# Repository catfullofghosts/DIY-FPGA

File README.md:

# diy_fpga
A discrete component FPGA designed from scratch

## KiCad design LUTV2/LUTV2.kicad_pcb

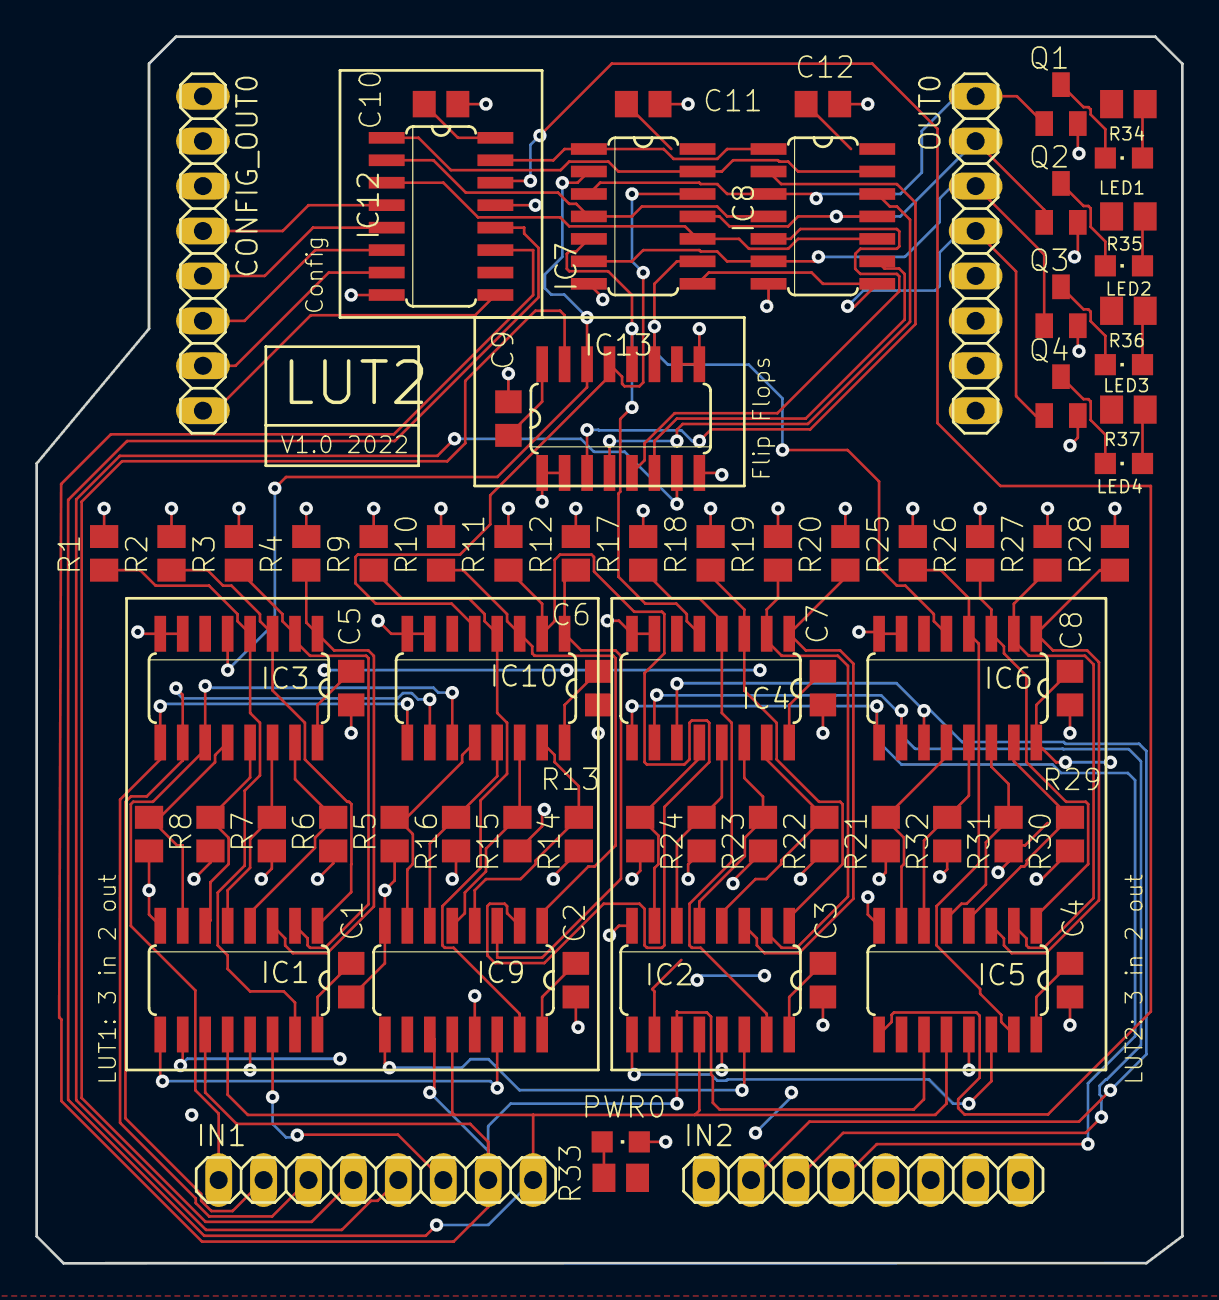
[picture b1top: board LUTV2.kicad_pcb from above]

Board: 2 copper layers, 64.8 x 69.3 mm, 74 parts (0 on the bottom side), 79 nets.

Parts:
C1, C2, C3, C4, C5, C6, C7, C8, C9, C10, C11, C12: C0805_348
CONFIG_OUT0: 1X08_325
IC1, IC2, IC5, IC9, IC12: 74HC595D; SO16
IC3, IC4, IC6, IC10: 74HC251D; SO16
IC7: 74HC126D; SO14
IC8: 74HC125D; SO14
IC13: 74HC173D; SO16
IN1, IN2: 1X08_325
LED1, LED2, LED3, LED4: CHIPLED_0805_420
OUT0: 1X08_325
PWR0: CHIPLED_0805_420
Q1, Q2, Q3, Q4: SOT23_420
R1, R2, R3, R4, R5, R6, R7, R8, R9, R10, R11, R12, R13, R14, R15, R16, R17, R18, R19, R20, R21, R22, R23, R24, R25, R26, R27, R28, R29, R30, R31, R32: M0805_348
R33, R34, R35, R36, R37: 220; M0805_348

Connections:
A: IC3.11, IC10.11, IN1.1
A2: IC4.11, IC6.11, IN2.2
ASYNC_0: IC7.1, IC8.1, IC12.15
ASYNC_1: IC7.13, IC8.13, IC12.1
ASYNC_2: IC7.4, IC8.4, IC12.2
ASYNC_3: IC7.10, IC8.10, IC12.3
B: IC3.10, IC10.10, IN1.2
B2: IC4.10, IC6.10, IN2.3
C: IC3.9, IC10.9, IN1.3
C2: IC4.9, IC6.9, IN2.4
DCLK: IC13.7, IN1.5
GND: C1.2, C2.2, C3.2, C4.2, C5.2, C6.2, C7.2, C8.2, C9.2, C10.2, C11.2, C12.2, CONFIG_OUT0.2, IC1.8, IC1.13, IC2.8, IC2.13, IC3.7, IC3.8, IC4.7, IC4.8, IC5.8, IC5.13, IC6.7, IC6.8, IC7.7, IC8.7, IC9.8, IC9.13, IC10.7, IC10.8, IC12.8, IC12.13, IC13.1, IC13.2, IC13.8, IC13.9, IC13.10, IN2.8, PWR0.C, Q1.2, Q2.2, Q3.2, Q4.2, R1.2, R2.2, R3.2, R4.2, R5.2, R6.2, R7.2, R8.2, R9.2, R10.2, R11.2, R12.2, R13.2, R14.2, R15.2, R16.2, R17.2, R18.2, R19.2, R20.2, R21.2, R22.2, R23.2, R24.2, R25.2, R26.2, R27.2, R28.2, R29.2, R30.2, R31.2, R32.2
LOAD: IC1.12, IC2.12, IC5.12, IC9.12, IC12.12, IN1.8
MISO: CONFIG_OUT0.8, IC12.9
MOSI: IC1.14, IN1.6
unnamed: IC1.15, IC3.4, R1.1
unnamed: IC1.1, IC3.3, R2.1
unnamed: IC1.2, IC3.2, R3.1
unnamed: IC1.4, IC3.15, R5.1
unnamed: IC1.5, IC3.14, R6.1
unnamed: IC1.6, IC3.13, R7.1
unnamed: IC1.7, IC3.12, R8.1
unnamed: IC3.5, IC7.2, IC13.14
unnamed: IC9.15, IC10.4, R9.1
unnamed: IC2.15, IC4.4, R17.1
unnamed: IC9.1, IC10.3, R10.1
unnamed: IC9.2, IC10.2, R11.1
unnamed: IC9.4, IC10.15, R13.1
unnamed: IC9.5, IC10.14, R14.1
unnamed: IC9.6, IC10.13, R15.1
unnamed: IC9.7, IC10.12, R16.1
unnamed: IC7.12, IC10.5, IC13.13
unnamed: IC1.9, IC9.14
unnamed: IC8.2, IC13.3
unnamed: IC2.14, IC9.9
unnamed: IC2.1, IC4.3, R18.1
unnamed: IC2.4, IC4.15, R21.1
unnamed: IC2.5, IC4.14, R22.1
unnamed: IC2.6, IC4.13, R23.1
unnamed: IC2.7, IC4.12, R24.1
unnamed: IC5.15, IC6.4, R25.1
unnamed: IC5.1, IC6.3, R26.1
unnamed: IC8.12, IC13.4
unnamed: IC9.3, IC10.1, R12.1
unnamed: IC1.3, IC3.1, R4.1
unnamed: IC5.4, IC6.15, R29.1
unnamed: IC5.5, IC6.14, R30.1
unnamed: IC5.6, IC6.13, R31.1
unnamed: IC5.7, IC6.12, R32.1
unnamed: IC2.9, IC5.14
unnamed: IC5.9, IC12.14
unnamed: IC6.5, IC7.9, IC13.11
unnamed: IC4.5, IC7.5, IC13.12
unnamed: IC5.2, IC6.2, R27.1
unnamed: IC5.3, IC6.1, R28.1
unnamed: IC2.2, IC4.2, R19.1
unnamed: IC2.3, IC4.1, R20.1
unnamed: CONFIG_OUT0.7, IC12.7
unnamed: CONFIG_OUT0.6, IC12.6
unnamed: CONFIG_OUT0.5, IC12.5
unnamed: CONFIG_OUT0.4, IC12.4
unnamed: IC8.5, IC13.5
unnamed: IC8.9, IC13.6
unnamed: PWR0.A, R33.1
unnamed: LED1.A, R34.1
unnamed: LED2.A, R35.1
unnamed: LED3.A, R36.1
unnamed: LED4.A, R37.1
unnamed: LED1.C, Q1.3
unnamed: LED2.C, Q2.3
unnamed: LED3.C, Q3.3
unnamed: LED4.C, Q4.3
O0: IC7.3, IC8.3, OUT0.1, Q1.1
O1: IC7.11, IC8.11, OUT0.2, Q2.1
O2: IC7.6, IC8.6, OUT0.3, Q3.1
O3: IC7.8, IC8.8, OUT0.4, Q4.1
RESET: IC13.15, IN1.4
SCK: IC1.11, IC2.11, IC5.11, IC9.11, IC12.11, IN1.7
VCC: C1.1, C2.1, C3.1, C4.1, C5.1, C6.1, C7.1, C8.1, C9.1, C10.1, C11.1, C12.1, CONFIG_OUT0.1, IC1.10, IC1.16, IC2.10, IC2.16, IC3.16, IC4.16, IC5.10, IC5.16, IC6.16, IC7.14, IC8.14, IC9.10, IC9.16, IC10.16, IC12.10, IC12.16, IC13.16, IN2.1, R33.2, R34.2, R35.2, R36.2, R37.2

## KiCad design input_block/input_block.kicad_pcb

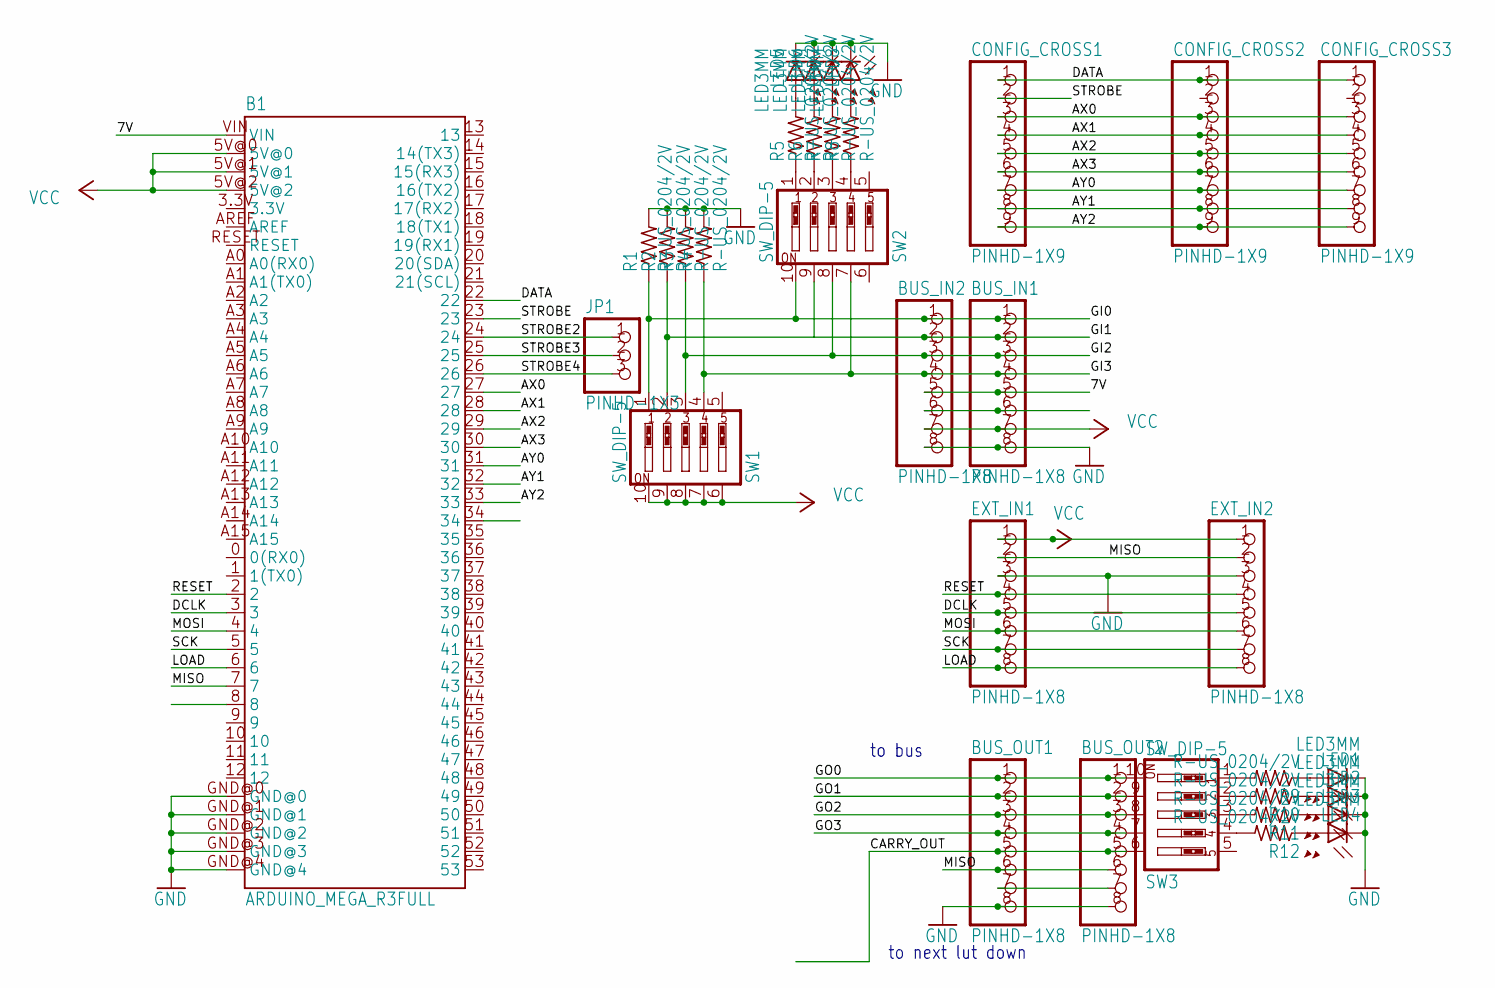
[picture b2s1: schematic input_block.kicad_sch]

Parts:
B1: ARDUINO_MEGA_R3FULL; ARDUINO_MEGA
BUS_IN1, BUS_IN2: PINHD-1X8; 1X08
BUS_OUT1, BUS_OUT2: PINHD-1X8; 1X08
CONFIG_CROSS1, CONFIG_CROSS2, CONFIG_CROSS3: PINHD-1X9; 1X09-BIG
EXT_IN1, EXT_IN2: PINHD-1X8; 1X08
JP1: PINHD-1X3; 1X03
LED1, LED2, LED3, LED4, LED5, LED6, LED7, LED8: LED3MM
R1, R2, R3, R4, R5, R6, R7, R8, R9, R10, R11, R12: R-US_0204/2V; 0204V
SW1, SW2, SW3: SW_DIP-5; EDG-05

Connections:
7V: B1.VIN, BUS_IN1.5, BUS_IN2.5
AX0: B1.27, CONFIG_CROSS1.3, CONFIG_CROSS2.3, CONFIG_CROSS3.3
AX1: B1.28, CONFIG_CROSS1.4, CONFIG_CROSS2.4, CONFIG_CROSS3.4
AX2: B1.29, CONFIG_CROSS1.5, CONFIG_CROSS2.5, CONFIG_CROSS3.5
AX3: B1.30, CONFIG_CROSS1.6, CONFIG_CROSS2.6, CONFIG_CROSS3.6
AY0: B1.31, CONFIG_CROSS1.7, CONFIG_CROSS2.7, CONFIG_CROSS3.7
AY1: B1.32, CONFIG_CROSS1.8, CONFIG_CROSS2.8, CONFIG_CROSS3.8
AY2: B1.33, CONFIG_CROSS1.9, CONFIG_CROSS2.9, CONFIG_CROSS3.9
CARRY_OUT: BUS_OUT1.5, BUS_OUT2.5, SW3.6
DATA: B1.22, CONFIG_CROSS1.1, CONFIG_CROSS2.1, CONFIG_CROSS3.1
DCLK: B1.3, EXT_IN1.5, EXT_IN2.5
GI0: BUS_IN1.1, BUS_IN2.1, R1.1, SW1.1, SW2.10
GI1: BUS_IN1.2, BUS_IN2.2, R2.1, SW1.2, SW2.9
GI2: BUS_IN1.3, BUS_IN2.3, R3.1, SW1.3, SW2.8
GI3: BUS_IN1.4, BUS_IN2.4, R4.1, SW1.4, SW2.7
GO0: BUS_OUT1.1, BUS_OUT2.1, SW3.10
GO1: BUS_OUT1.2, BUS_OUT2.2, SW3.9
GO2: BUS_OUT1.3, BUS_OUT2.3, SW3.8
GO3: BUS_OUT1.4, BUS_OUT2.4, SW3.7
LOAD: B1.6, EXT_IN1.8, EXT_IN2.8
MISO: B1.7, BUS_OUT1.6, BUS_OUT2.6, EXT_IN1.2, EXT_IN2.2
MOSI: B1.4, EXT_IN1.6, EXT_IN2.6
unnamed: BUS_IN1.6, BUS_IN2.6
unnamed: BUS_OUT1.7, BUS_OUT2.7
unnamed: LED5.A, R5.2
unnamed: R5.1, SW2.1
unnamed: LED6.A, R6.2
unnamed: R6.1, SW2.2
unnamed: LED7.A, R7.2
unnamed: R7.1, SW2.3
unnamed: LED8.A, R8.2
unnamed: R8.1, SW2.4
unnamed: LED1.A, R9.1
unnamed: LED2.A, R10.1
unnamed: LED3.A, R11.1
unnamed: LED4.A, R12.1
unnamed: R9.2, SW3.1
unnamed: R10.2, SW3.2
unnamed: R11.2, SW3.3
unnamed: R12.2, SW3.4
SCK: B1.5, EXT_IN1.7, EXT_IN2.7
STROBE: B1.23, CONFIG_CROSS1.2
STROBE2: B1.24, JP1.1
STROBE3: B1.25, JP1.2
STROBE4: B1.26, JP1.3
VCC: B1.5V@0, B1.5V@1, B1.5V@2, BUS_IN1.7, BUS_IN2.7, EXT_IN1.1, EXT_IN2.1, SW1.6, SW1.7, SW1.8, SW1.9, SW1.10

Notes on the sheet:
to next lut down
to bus

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
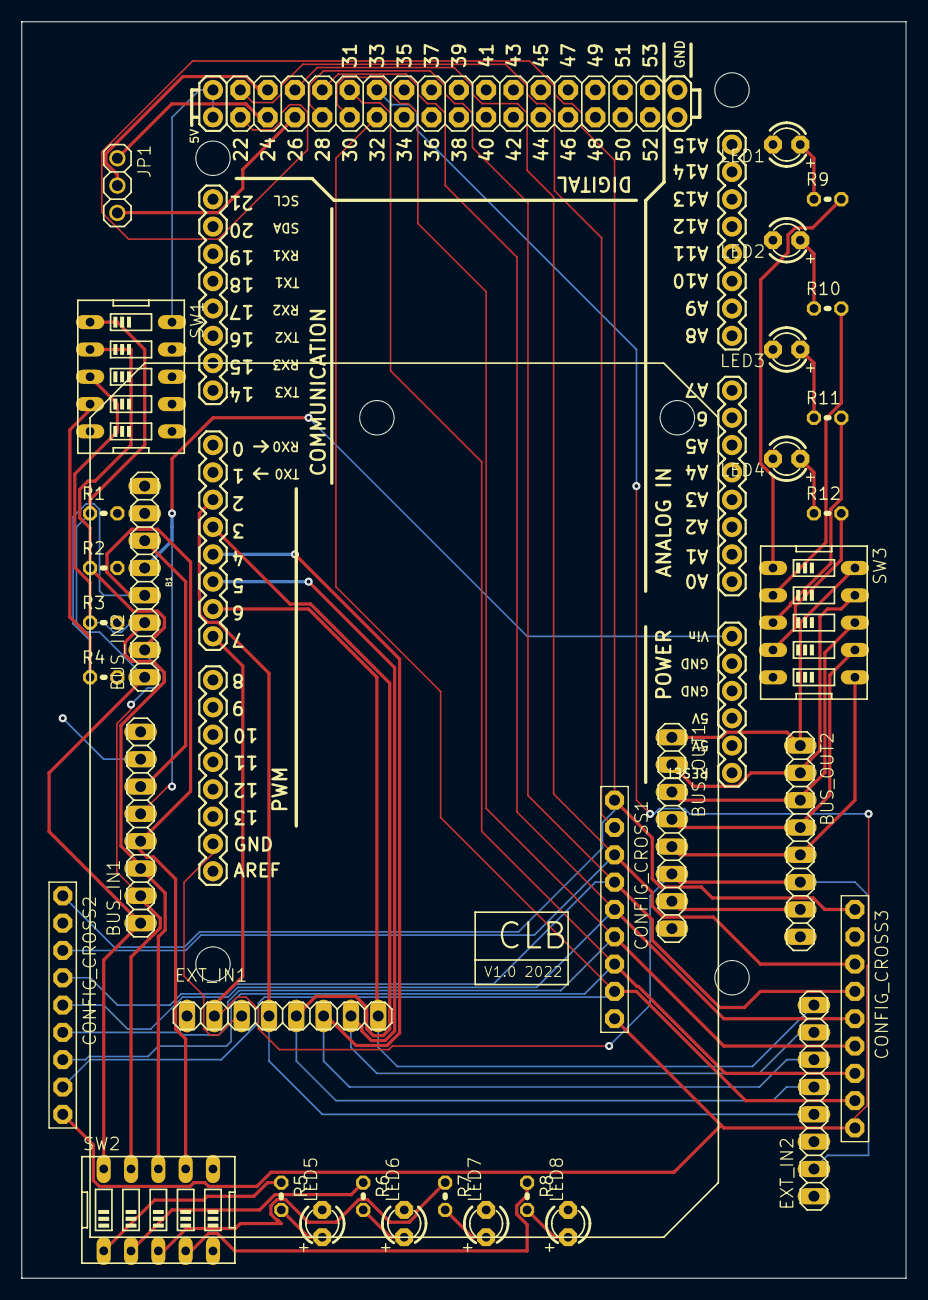
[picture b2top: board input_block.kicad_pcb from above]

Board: 2 copper layers, 82.2 x 116.8 mm, 34 parts (0 on the bottom side), 48 nets.

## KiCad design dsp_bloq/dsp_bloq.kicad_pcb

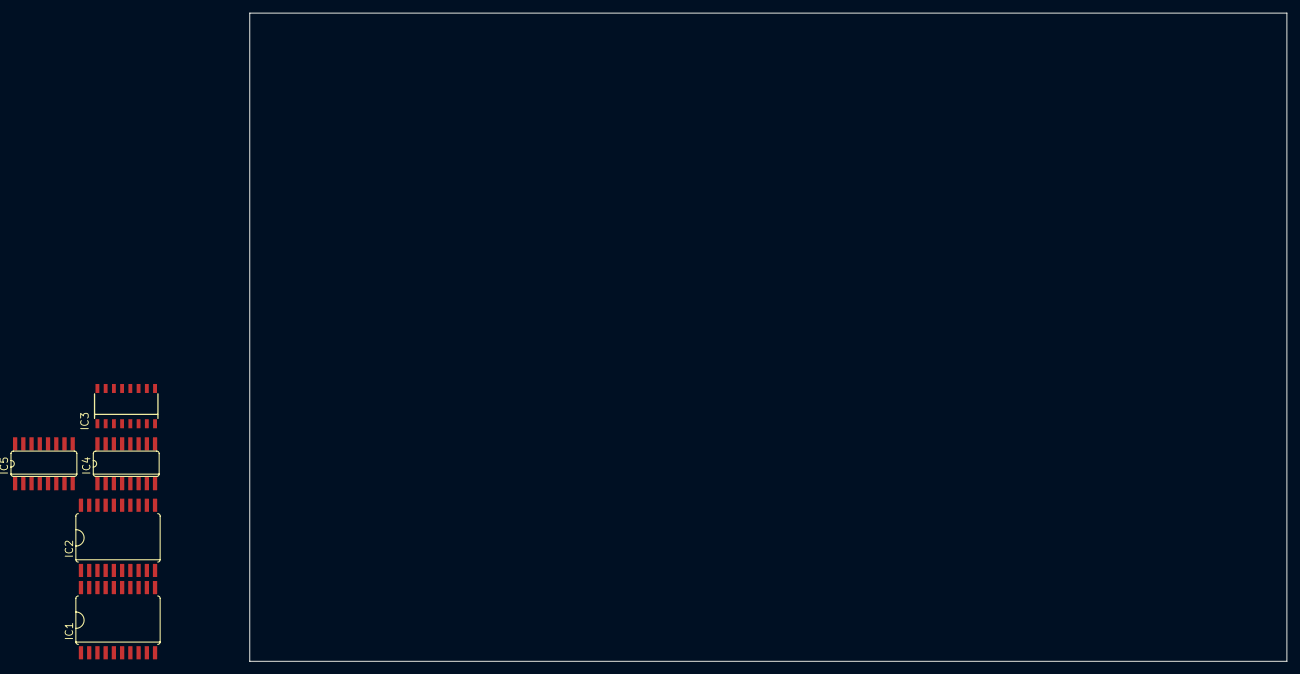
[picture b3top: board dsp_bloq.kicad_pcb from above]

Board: 2 copper layers, 160.0 x 100.0 mm, 5 parts (0 on the bottom side), 4 nets, no tracks yet.

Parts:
IC1: 74LS381DW; SO20W_88
IC2: 74274J; SO20W_88
IC3: 74HC191D; SO16D_88
IC4, IC5: 74LS153D; SO16_88

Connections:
GND: IC1.10, IC2.10, IC3.8, IC4.8, IC5.8
OUT_0: IC4.14, IC5.14
OUT_1: IC4.2, IC5.2
VCC: IC1.20, IC2.20, IC3.16, IC4.16, IC5.16
